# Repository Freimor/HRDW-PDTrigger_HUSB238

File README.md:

## PD Trigger module on Hynetek HUSB238 chip
This is a rework of [Hynetek HUSB238 evaluation board](https://www.hynetek.com/uploadfiles/site/219/files/23877051-9b40-4ae7-b10f-7e32536c2083.pdf) with minor changes. In general, i just added a fuse and reroute schematic for using available components from AliExpress.

The project is completed in Q4 2022.

## Parameters for PCB order (JLCPCB compatible)
2 layer board

0.8mm thickness

0.25mm min hole size

Castellated holes

## BOM list
| №  | Designator  | Qty | Description        | Manufacturer  | Name           | Package  | Link |
| -- | ----------- | --- | ------------------ | ------------- | -------------- | -------- | ---- |
| 1  | C1, C2      | 2   | 330pf MLCC         |               |                | 0402     |      |
| 2  | C3          | 1   | 1uF MLCC           |               |                | 0402     |      |
| 3  | R1          | 1   | 100kΩ smd resistor |               |                | 0402     |      |
| 4  | R2          | 1   | 10Ω smd resistor   |               |                | 0402     |      |
| 5  | R3          | 1   | 30kΩ smd resistor  |                |                | 0402     |      |
| 6  | R4, R5      | 2   | Choose a value based on the output characteristics  |    |            | 0805     |      |
| 7  | R6          | 1   | 1MΩ smd resistor   |               |                | 0402     |      |
| 8  | D1,D2,D3,D4 | 4   | TVS diod           | Littelfuse    | PGB1010603     | 0603     | [AliExpress](https://aliexpress.ru/item/32895822186.html)      |
| 9  | F1          | 1   | SMD Fuse           |               |                | 1808     | [AliExpress](https://aliexpress.ru/item/33048094198.html)      |
| 10 | J5          | 1   | USB Type-C 16pin   | GCT           | USB4505-03-0-A |          | [AliExpress](https://aliexpress.ru/item/33013020868.html)      |
| 11 | Q1          | 1   | P-MOSFET 30V       | Alpha & Omega | AON7403        | DFN3x3EP | [AliExpress](https://aliexpress.ru/item/1005003805312191.html) |
| 12 | U1          | 1   | PD controller      | Hynetek       | HUSB238        | DFN-10   | [AliExpress](https://aliexpress.ru/item/1005002906568952.html) |

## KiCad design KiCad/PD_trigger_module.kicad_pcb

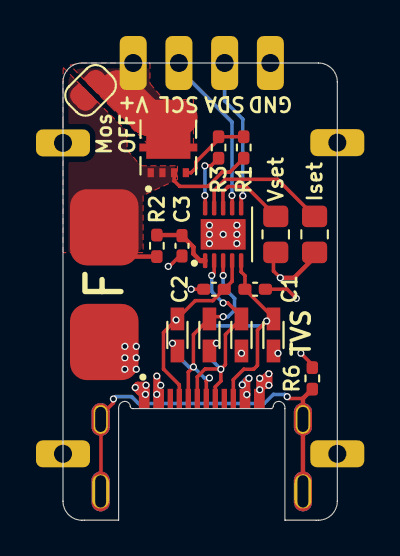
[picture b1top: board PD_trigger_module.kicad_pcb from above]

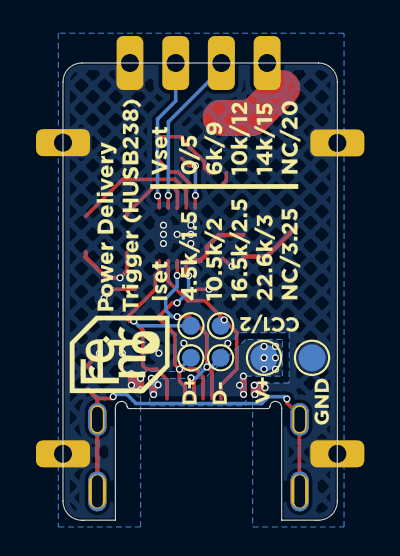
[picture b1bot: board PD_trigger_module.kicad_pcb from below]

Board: 2 copper layers, 15.2 x 25.4 mm, 33 parts (7 on the bottom side), 16 nets.

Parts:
C1, C2: 330pF; C_0402_1005Metric_Pad0.74x0.62mm_HandSolder
C3: 1uF; C_0402_1005Metric_Pad0.74x0.62mm_HandSolder
CC1, CC1/2-: TestPoint_Pad_D1.0mm
D1, D2, D3, D4: D_TVS; ESD_PGB1010603MR
D+: TestPoint_Pad_D1.0mm
D-: TestPoint_Pad_D1.0mm
F1: Fuse_Small; FuseHolder_1808
GND: Conn_01x01_Female; Castellated_hole_2.54
GND#2: TestPoint_Pad_D1.5mm
Iset: Iset; R_0805_2012Metric_Pad1.20x1.40mm_HandSolder
J2, J2#2, J2#3, J2#4: Conn_01x01_Female; Castellated_hole_2.54
J5: USB_C_Receptacle_USB2.0; TYPE_C_GCT_USB4505-03-0-A
JP1: SolderJumper_2_Open; SolderJumper-2_P1.3mm_Open_RoundedPad1.0x1.5mm
Q1: AON7403
R1: 100k; R_0402_1005Metric_Pad0.72x0.64mm_HandSolder
R2: 10; R_0402_1005Metric_Pad0.72x0.64mm_HandSolder
R3: 30k; R_0402_1005Metric_Pad0.72x0.64mm_HandSolder
R6: 1M; R_0402_1005Metric_Pad0.72x0.64mm_HandSolder
Ref**: Val**; drawing
SCL: Conn_01x01_Female; Castellated_hole_2.54
SDA: Conn_01x01_Female; Castellated_hole_2.54
U1: HUSB238; HUSB238_Hynetek
V+: Conn_01x01_Female; Castellated_hole_2.54
V+#2: TestPoint_Pad_D1.5mm
Vset: Vset; R_0805_2012Metric_Pad1.20x1.40mm_HandSolder

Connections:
unnamed: C1.1, CC1/2-.1, D3.2 (A2), J5.B5 (CC2), U1.5 (CC2)
unnamed: C2.1, CC1.1, D4.2 (A2), J5.A5 (CC1), U1.4 (CC1)
unnamed: C3.1, R2.2, U1.1 (VIN)
unnamed: D1.2 (A2), D+.1, J5.A6 (D+), J5.B6 (D+), U1.2 (D+)
unnamed: D2.2 (A2), D-.1, J5.A7 (D-), J5.B7 (D-), U1.3 (D-)
unnamed: F1.1, J5.A4 (VBUS), J5.A9 (VBUS), J5.B4 (VBUS), J5.B9 (VBUS), V+#2.1
unnamed: F1.2, JP1.1 (A), Q1.1 (S), Q1.2 (S), Q1.3 (S), R1.1, R2.1
unnamed: J5.S1 (SHIELD), R6.1
unnamed: Q1.4 (G), R1.2, R3.1
unnamed: R3.2, U1.10 (GATE)
unnamed: U1.8 (Vset), Vset.1
unnamed: Iset.1, U1.9 (Iset)
SCL: SCL.1, U1.7 (SCL)
SDA: SDA.1, U1.6 (SDA)
Vdd: C1.2, C2.2, C3.2, D1.1 (A1), D2.1 (A1), D3.1 (A1), D4.1 (A1), GND.1, GND#2.1, Iset.2, J2.1, J2#2.1, J2#3.1, J2#4.1, J5.A1 (GND), J5.A12 (GND), J5.B1 (GND), J5.B12 (GND), R6.2, U1.11 (GND), Vset.2
Vss: JP1.2 (B), Q1.5 (D), Q1.6 (D), Q1.7 (D), Q1.8 (D), V+.1

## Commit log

2022-09-27 Add KiCad files
2022-09-27 Add BOM list to README
2022-09-28 Updata data
2022-09-28 Some minor corrections
2022-09-28 Add pics
2022-09-30 Design update
2022-10-01 Add LICENSE
